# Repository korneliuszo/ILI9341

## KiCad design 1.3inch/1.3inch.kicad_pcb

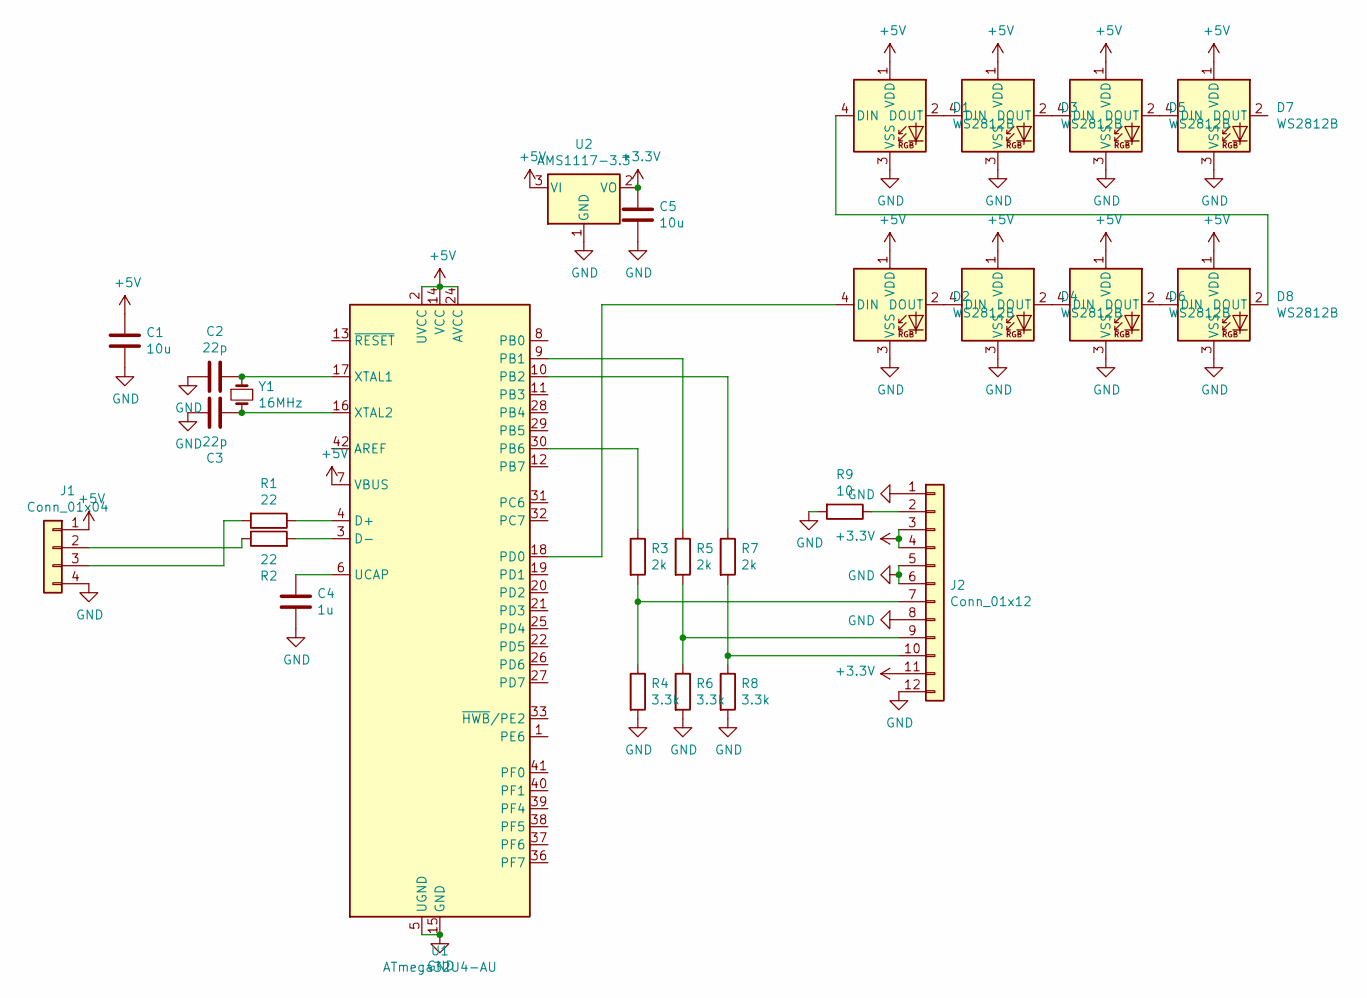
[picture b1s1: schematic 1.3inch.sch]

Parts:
C1, C5: 10u; C_0805_2012Metric_Pad1.15x1.40mm_HandSolder
C2, C3: 22p; C_0805_2012Metric_Pad1.15x1.40mm_HandSolder
C4: 1u; C_0805_2012Metric_Pad1.15x1.40mm_HandSolder
D1, D2, D3, D4, D5, D6, D7, D8: WS2812B; LED_WS2812B_PLCC4_5.0x5.0mm_P3.2mm
J1: Conn_01x04; JST_GH_SM04B-GHS-TB_1x04-1MP_P1.25mm_Horizontal
J2: Conn_01x12; FPC_12
R1, R2: 22; R_0805_2012Metric_Pad1.15x1.40mm_HandSolder
R3, R5, R7: 2k; R_0805_2012Metric_Pad1.15x1.40mm_HandSolder
R4, R6, R8: 3.3k; R_0805_2012Metric_Pad1.15x1.40mm_HandSolder
R9: 10; R_0805_2012Metric_Pad1.15x1.40mm_HandSolder
U1: ATmega32U4-AU; TQFP-44_10x10mm_P0.8mm
U2: AMS1117-3.3; SOT-223-3_TabPin2
Y1: 16MHz; Crystal_SMD_5032-2Pin_5.0x3.2mm_HandSoldering

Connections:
+3V3: C5.1, J2.3, J2.4, J2.11, U2.2 (VO)
+5V: C1.1, D1.1 (VDD), D2.1 (VDD), D3.1 (VDD), D4.1 (VDD), D5.1 (VDD), D6.1 (VDD), D7.1 (VDD), D8.1 (VDD), J1.1, U1.2 (UVCC), U1.7 (VBUS), U1.14 (VCC), U1.24 (AVCC), U1.34 (VCC), U1.44 (AVCC), U2.3 (VI)
GND: C1.2, C2.2, C3.2, C4.2, C5.2, D1.3 (VSS), D2.3 (VSS), D3.3 (VSS), D4.3 (VSS), D5.3 (VSS), D6.3 (VSS), D7.3 (VSS), D8.3 (VSS), J1.4, J2.1, J2.5, J2.6, J2.8, J2.12, R4.2, R6.2, R8.2, R9.2, U1.5 (UGND), U1.15 (GND), U1.23 (GND), U1.35 (GND), U1.43 (GND), U2.1 (GND)
unnamed: C2.1, U1.17 (XTAL1), Y1.1
unnamed: C3.1, U1.16 (XTAL2), Y1.2
unnamed: C4.1, U1.6 (UCAP)
unnamed: D1.2 (DOUT), D3.4 (DIN)
unnamed: D1.4 (DIN), D8.2 (DOUT)
unnamed: D2.2 (DOUT), D4.4 (DIN)
unnamed: D2.4 (DIN), U1.18 (PD0)
unnamed: D3.2 (DOUT), D5.4 (DIN)
unnamed: D4.2 (DOUT), D6.4 (DIN)
unnamed: D5.2 (DOUT), D7.4 (DIN)
unnamed: D6.2 (DOUT), D8.4 (DIN)
unnamed: J1.2, R2.1
unnamed: J1.3, R1.2
unnamed: J2.2, R9.1
unnamed: J2.7, R3.2, R4.1
unnamed: J2.9, R5.2, R6.1
unnamed: J2.10, R7.2, R8.1
unnamed: R1.1, U1.4 (D+)
unnamed: R2.2, U1.3 (D-)
unnamed: R3.1, U1.30 (PB6)
unnamed: R5.1, U1.9 (PB1)
unnamed: R7.1, U1.10 (PB2)

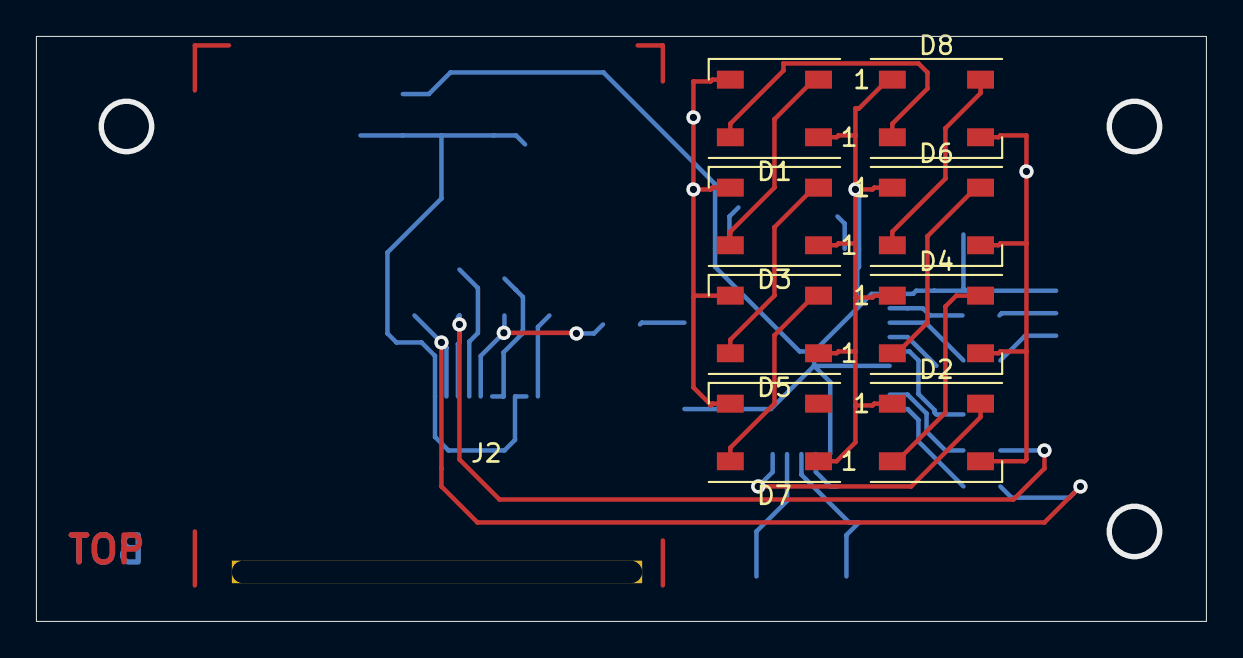
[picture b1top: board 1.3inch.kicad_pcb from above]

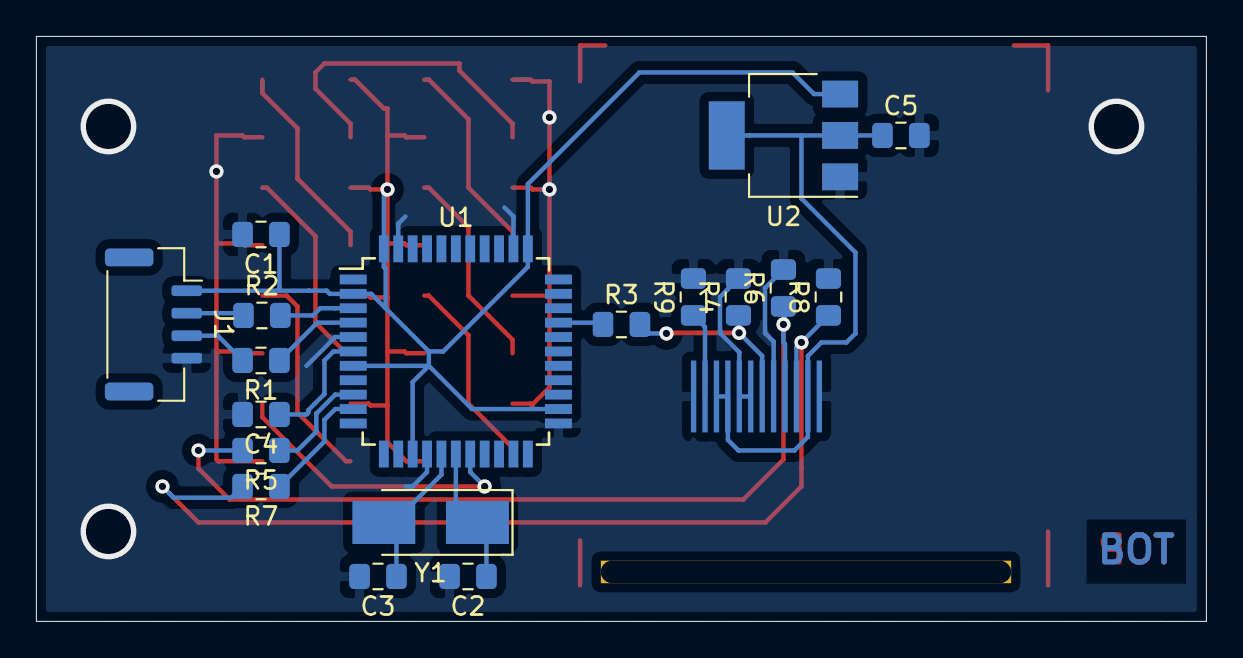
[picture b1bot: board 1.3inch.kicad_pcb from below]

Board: 2 copper layers, 65.0 x 32.5 mm, 27 parts (18 on the bottom side), 25 nets.

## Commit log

2019-11-22 First commit with working entering bootloader
2019-11-22 Add drawing from usb support
2019-11-22 Add lcd4linux
2019-11-22 su: lcd4linux
2019-11-22 Now USB API contains dimensions ... maybe small changes only in fw to support other displays?
2019-11-23 Add WS2812 support
2020-01-24 Same driver different display
2020-02-03 Add pinebook internal pcb
2020-02-08 Add warnings
2020-02-14 Add schematics in PDF
